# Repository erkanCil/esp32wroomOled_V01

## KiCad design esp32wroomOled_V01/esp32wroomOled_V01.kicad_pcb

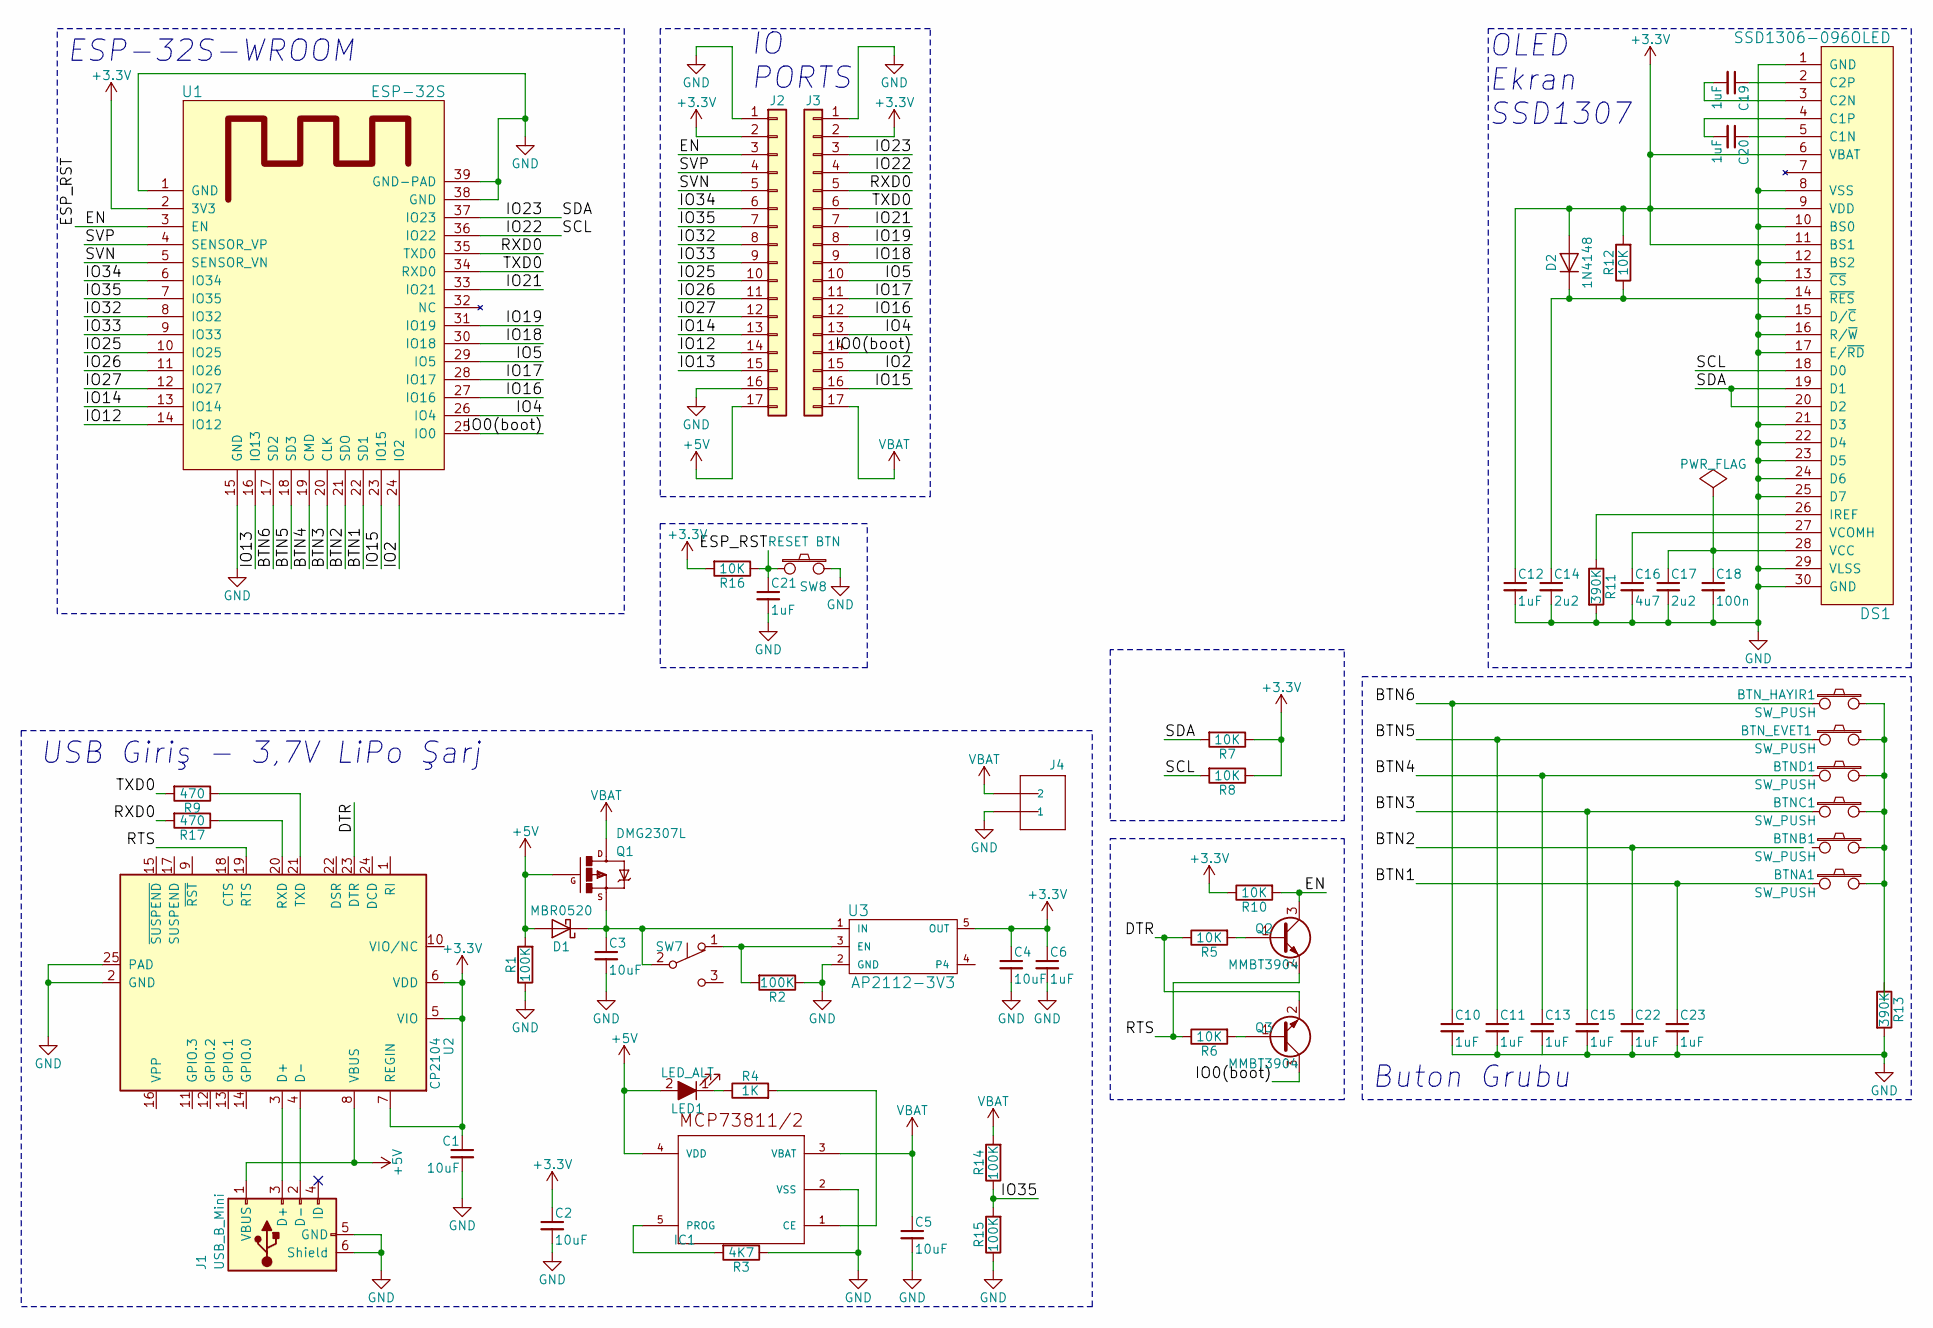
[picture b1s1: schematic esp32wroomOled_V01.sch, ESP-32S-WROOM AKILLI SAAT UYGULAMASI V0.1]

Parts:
BTNA1: SW_PUSH; Tact_Switch_Top_PTS820
BTNB1: SW_PUSH; Tact_Switch_Top_PTS820
BTNC1: SW_PUSH; Tact_Switch_Top_PTS820
BTND1: SW_PUSH; Tact_Switch_Top_PTS820
BTN_EVET1: SW_PUSH; Tact_Switch_Top_PTS820
BTN_HAYIR1: SW_PUSH; Tact_Switch_Top_PTS820
C1, C2, C3, C4, C5: 10uF; c_0603
C6, C10, C11, C12, C13, C15, C19, C20, C21, C22, C23: 1uF; c_0603
C14, C17: 2u2; c_0603
C16: 4u7; c_0603
C18: 100n; c_0603
D1: MBR0520; D_SOD-123
D2: 1N4148; sod323
DS1: SSD1306-096OLED
IC1: MCP73811_2; sot23-5
J1: USB_B_Mini; USB_Micro-B_10103594-0001LF
J2, J3: Conn_01x17; pin_strip_17
J4: JST_2MM_MALE; df13-2p-125ds
LED1: LED_ALT; LED_0805
Q1: DMG2307L; sot23
Q2, Q3: MMBT3904; SOT-23
R1, R2, R14, R15: 100K; r_0603
R3: 4K7; r_0603
R4: 1K; r_0603
R5, R6, R7, R8, R10, R12, R16: 10K; r_0603
R9, R17: 470; r_0603
R11, R13: 390K; r_0603
SW7: SW_Push_SPDT; switch_mmp122-r
SW8: RESET BTN; Tact_Switch_Top_PTS820
U1: ESP-32S; ESP32-WROOM
U2: CP2104; QFN-24-1EP_4x4mm_Pitch0.5mm
U3: AP2112-3V3; sot23-5

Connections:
+3V3: C1.1, C2.1, C4.1, C6.1, C12.1, D2.2 (A), DS1.6 (VBAT), DS1.9 (VDD), DS1.11 (BS1), J2.2, J3.2, R7.1, R8.1, R10.1, R12.2, R16.2, U1.2 (3V3), U2.5 (VIO), U2.6 (VDD), U2.7 (REGIN), U3.5 (OUT)
+5V: D1.2 (A), IC1.4 (VDD), J1.1 (VBUS), J2.17, LED1.2 (A), Q1.1 (G), R1.2, U2.8 (VBUS)
/BTN1: BTNA1.1, C23.1, U1.22 (SD1)
/BTN2: C22.1, U1.21 (SDO)
/BTN3: BTNC1.1, C15.1, U1.20 (CLK)
/BTN4: BTND1.1, C13.1, U1.19 (CMD)
/BTN5: BTN_EVET1.1, C11.1, U1.18 (SD3)
/BTN6: BTN_HAYIR1.1, C10.1, U1.17 (SD2)
/DTR: Q3.2 (E), R5.1, U2.23 (DTR)
/EN: C21.1, J2.3, Q2.3 (C), R10.2, R16.1, SW8.1, U1.3 (EN)
/IO0(boot): J3.14, Q3.3 (C), U1.25 (IO0)
/IO2: J3.15, U1.24 (IO2)
/IO4: J3.13, U1.26 (IO4)
/IO5: J3.10, U1.29 (IO5)
/IO12: J2.14, U1.14 (IO12)
/IO13: J2.15, U1.16 (IO13)
/IO14: J2.13, U1.13 (IO14)
/IO15: J3.16, U1.23 (IO15)
/IO16: J3.12, U1.27 (IO16)
/IO17: J3.11, U1.28 (IO17)
/IO18: J3.9, U1.30 (IO18)
/IO19: J3.8, U1.31 (IO19)
/IO21: J3.7, U1.33 (IO21)
/IO22: DS1.18 (D0), J3.4, R8.2, U1.36 (IO22)
/IO23: DS1.19 (D1), DS1.20 (D2), J3.3, R7.2, U1.37 (IO23)
/IO25: J2.10, U1.10 (IO25)
/IO26: J2.11, U1.11 (IO26)
/IO27: J2.12, U1.12 (IO27)
/IO32: J2.8, U1.8 (IO32)
/IO33: J2.9, U1.9 (IO33)
/IO34: J2.6, U1.6 (IO34)
/IO35: J2.7, R14.1, R15.2, U1.7 (IO35)
/RTS: Q2.2 (E), R6.1, U2.19 (RTS)
/RXD0: J3.5, R17.2, U1.35 (TXD0)
/SVN: J2.5, U1.5 (SENSOR_VN)
/SVP: J2.4, U1.4 (SENSOR_VP)
/TXD0: J3.6, R9.2, U1.34 (RXD0)
GND: C1.2, C2.2, C3.2, C4.2, C5.2, C6.2, C10.2, C11.2, C12.2, C14.2, C15.2, C16.2, C17.2, C18.2, C21.2, C22.2, C23.2, DS1.1 (GND), DS1.8 (VSS), DS1.10 (BS0), DS1.12 (BS2), DS1.13 (~CS), DS1.15 (D/~C), DS1.16 (R/~W), DS1.17 (E/~RD), DS1.21 (D3), DS1.22 (D4), DS1.23 (D5), DS1.24 (D6), DS1.25 (D7), DS1.29 (VLSS), DS1.30 (GND), IC1.2 (VSS), J1.5 (GND), J1.6 (Shield), J2.1, J2.16, J3.1, J4.1, R1.1, R2.1, R3.1, R11.2, R13.2, R15.1, SW8.2, U1.1 (GND), U1.15 (GND), U1.38 (GND), U1.39 (GND-PAD), U2.2 (GND), U2.25 (PAD), U3.2 (GND)
unnamed: BTNA1.2, BTNB1.2, BTNC1.2, BTND1.2, BTN_EVET1.2, BTN_HAYIR1.2
unnamed: C3.1, D1.1 (K), Q1.2 (S), SW7.2 (B), U3.1 (IN)
unnamed: C14.1, D2.1 (K), DS1.14 (~RES), R12.1
unnamed: C16.1, DS1.27 (VCOMH)
unnamed: C17.1, C18.1, DS1.28 (VCC)
unnamed: C19.1, DS1.2 (C2P)
unnamed: C19.2, DS1.3 (C2N)
unnamed: C20.1, DS1.5 (C1N)
unnamed: C20.2, DS1.4 (C1P)
unnamed: DS1.26 (IREF), R11.1
unnamed: IC1.1 (CE), R4.2
unnamed: IC1.5 (PROG), R3.2
unnamed: J1.2 (D-), U2.4 (D-)
unnamed: J1.3 (D+), U2.3 (D+)
unnamed: LED1.1 (K), R4.1
unnamed: Q2.1 (B), R5.2
unnamed: Q3.1 (B), R6.2
unnamed: R2.2, SW7.1 (A), U3.3 (EN)
unnamed: R9.1, U2.21 (TXD)
unnamed: R17.1, U2.20 (RXD)
VBAT: C5.1, IC1.3 (VBAT), J3.17, J4.2, Q1.3 (D), R14.2

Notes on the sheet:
USB Giriş - 3,7V LiPo Şarj
Buton Grubu
OLED Ekran SSD1307
IO PORTS
ESP-32S-WROOM

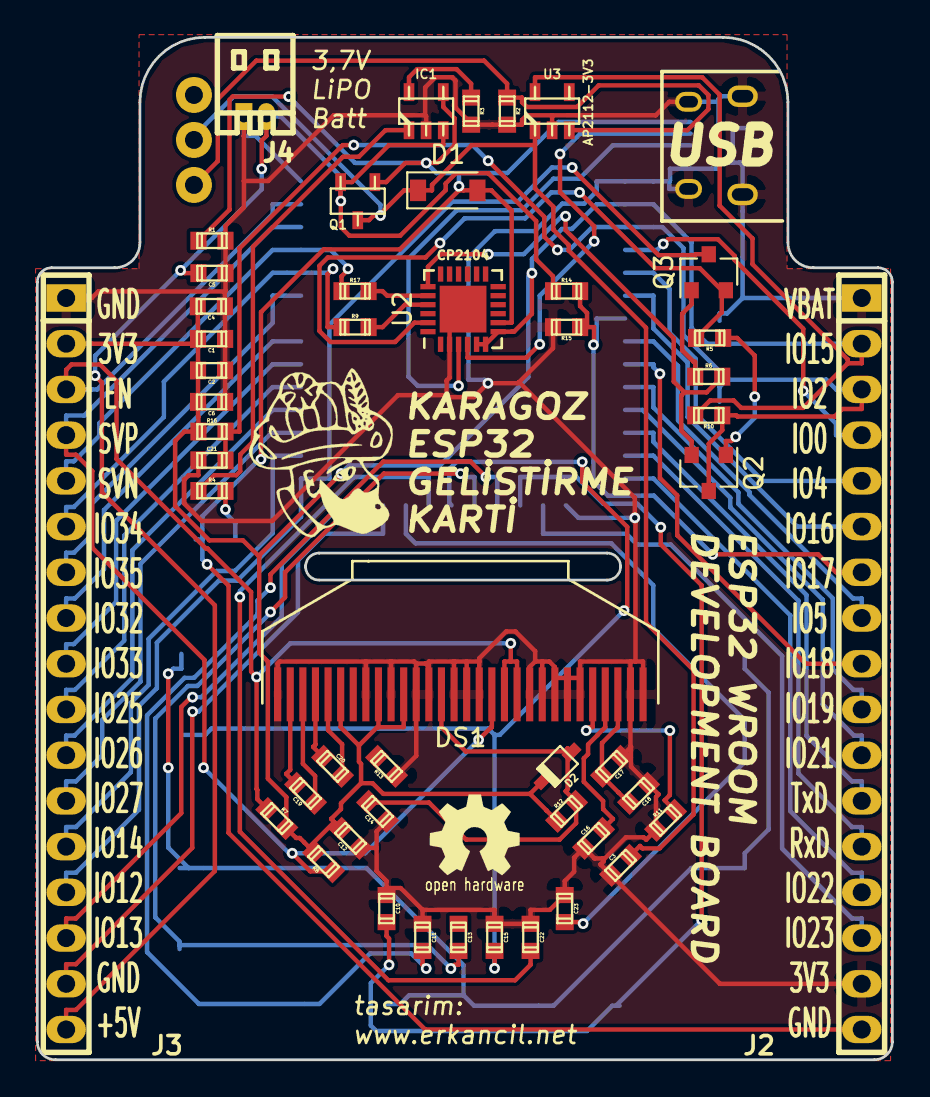
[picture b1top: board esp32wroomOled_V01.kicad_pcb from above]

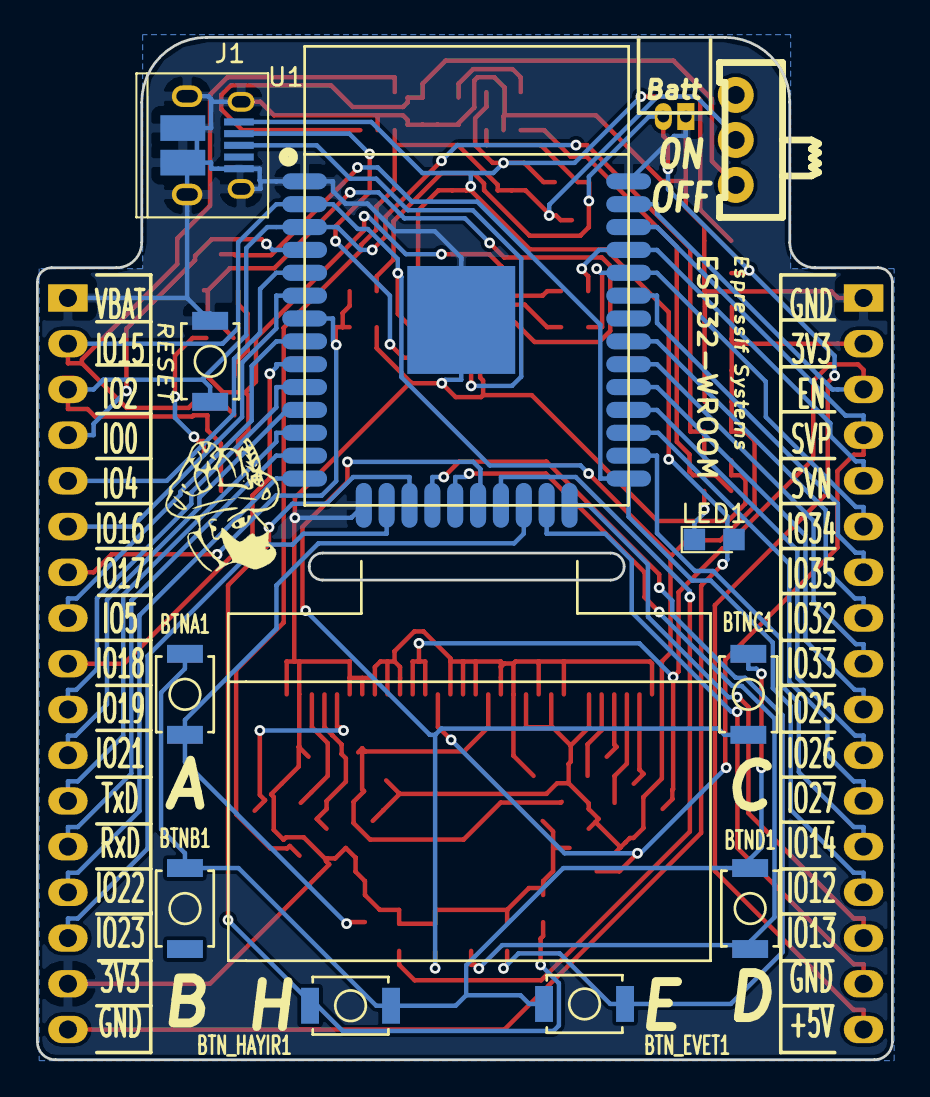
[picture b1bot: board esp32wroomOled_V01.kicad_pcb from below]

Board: 2 copper layers, 47.5 x 56.8 mm, 62 parts (12 on the bottom side), 59 nets.

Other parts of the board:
G1: LOGO; karaGoz_08mm
G2: LOGO; karaGoz_10mm

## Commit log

2017-12-04 :circus_tent: Added .gitattributes & .gitignore files
